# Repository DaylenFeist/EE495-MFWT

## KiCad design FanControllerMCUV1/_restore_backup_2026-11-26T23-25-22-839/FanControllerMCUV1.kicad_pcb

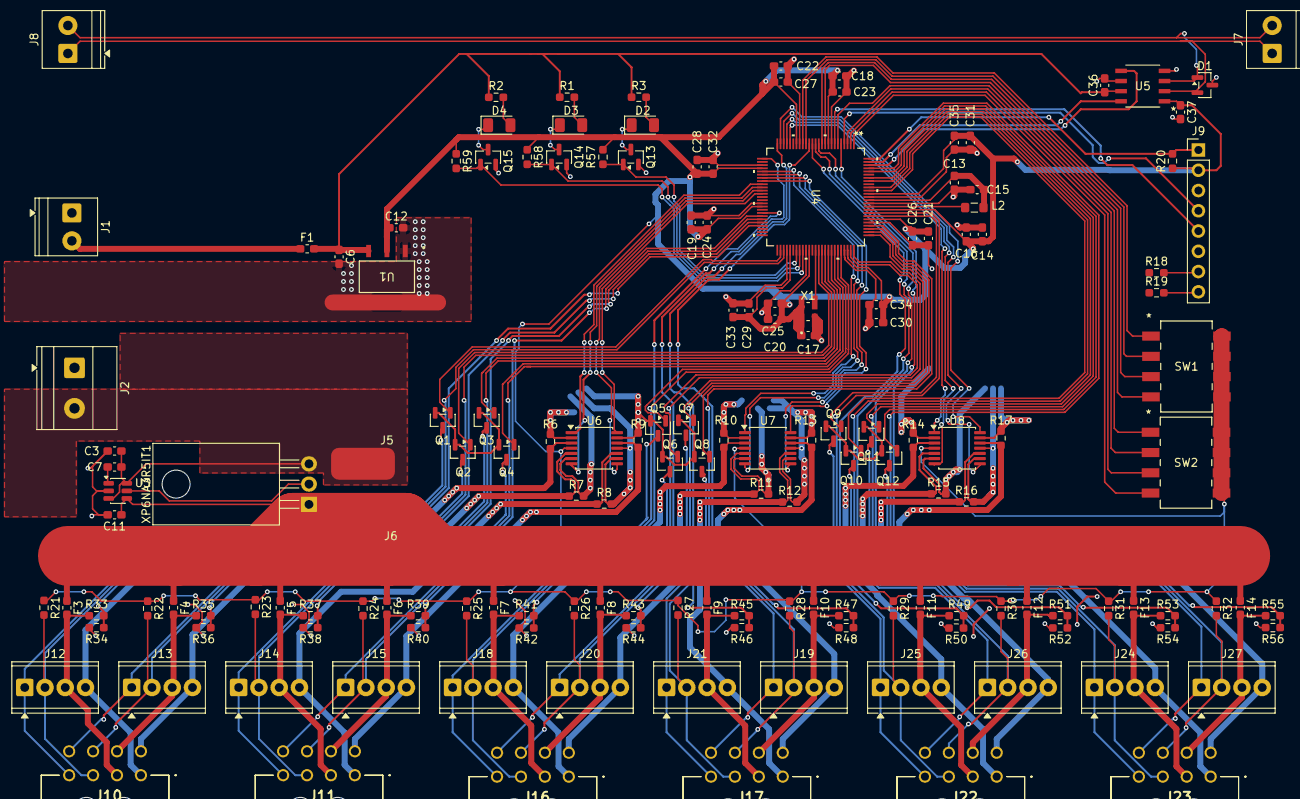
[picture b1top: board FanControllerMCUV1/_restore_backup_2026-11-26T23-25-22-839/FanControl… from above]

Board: 2 copper layers, 156 parts (0 on the bottom side), 121 nets.

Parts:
C3, C7, C11, C15, C16, C17, C18, C19, C20, C21, C23, C24, C25, C26, C27, C28, C29, C30, C31, C32, C33, C34, C35: 0.1u; C_0603_1608Metric_Pad1.08x0.95mm_HandSolder
C6, C12, C13, C14: 10u; C_0603_1608Metric_Pad1.08x0.95mm_HandSolder
C22: 1u; C_0603_1608Metric_Pad1.08x0.95mm_HandSolder
C36, C37: .1u; C_0603_1608Metric_Pad1.08x0.95mm_HandSolder
D1: NUP2105L; SOT-23
D2: GLED; LED_1206_3216Metric
D3: YLED; LED_1206_3216Metric
D4: RLED; LED_1206_3216Metric
F1, F3, F4, F5, F6, F7, F8, F9, F10, F11, F12, F13, F14: Fuse; Fuse_0603_1608Metric_Pad1.05x0.95mm_HandSolder
J1: Screw_Terminal_01x02; TerminalBlock_Phoenix_PT-1,5-2-3.5-H_1x02_P3.50mm_Horizontal
J2: Screw_Terminal_01x02; TerminalBlock_Phoenix_MKDS-1,5-2-5.08_1x02_P5.08mm_Horizont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
J5, J6: Conn_01x01_Pin; SolderWirePad_1x01_SMD_4x8mm
J7: CAN-IN; TerminalBlock_Phoenix_PT-1,5-2-3.5-H_1x02_P3.50mm_Horizontal
J8: CAN-OUT; TerminalBlock_Phoenix_PT-1,5-2-3.5-H_1x02_P3.50mm_Horizontal
J9: Conn_01x08_Pin; PinHeader_1x08_P2.54mm_Vertical
J10, J11, J16, J17, J22, J23: 3-794618-8; 37946188
J12, J13, J14, J15, J18, J19, J20, J21, J24, J25, J26, J27: Screw_Terminal_01x04; TerminalBlock_Phoenix_MPT-0,5-4-2.54_1x04_P2.54mm_Horizontal
L2: SRN2012T-100K; L_0805_2012Metric_Pad1.05x1.20mm_HandSolder
Q1, Q2, Q3, Q4, Q5, Q6, Q7, Q8, Q9, Q10, Q11, Q12, Q13, Q14, Q15: 2N7002; SOT-23
R1, R2: 300; R_0603_1608Metric_Pad0.98x0.95mm_HandSolder
R3: 180; R_0603_1608Metric_Pad0.98x0.95mm_HandSolder
R6, R7, R8, R9, R10, R11, R12, R13, R14, R15, R16, R17: 20m; R_0603_1608Metric_Pad0.98x0.95mm_HandSolder
R18, R19: DNP; R_0603_1608Metric_Pad0.98x0.95mm_HandSolder
R20, R21, R22, R23, R24, R25, R26, R27, R28, R29, R30, R31, R32, R34, R36, R38, R40, R42, R44, R46, R48, R50, R52, R54, R56: 10k; R_0603_1608Metric_Pad0.98x0.95mm_HandSolder
R33, R35, R37, R39, R41, R43, R45, R47, R49, R51, R53, R55: 240k; R_0603_1608Metric_Pad0.98x0.95mm_HandSolder
R57, R58, R59: 100k; R_0603_1608Metric_Pad0.98x0.95mm_HandSolder
SW1, SW2: SW_DIP_x04; DS04-254-2-04BK-SMT_CUD
U1: NCP1117ST33T3G; SOT223-3_ONS
U3: LM74700; SOT-23-6
U4: dsPIC33AK512MC510-I/PT; TQFP100_PT_MCH
U5: TCAN1462VDRQ1; SOIC8_D_TEX
U6, U7, U8: INA4180A2; TSSOP-14_4.4x5mm_P0.65mm
X1: DSC6011JI2B-008.0000; VLGA4_AUA_MCH
XP6NA3R5IT1: NMOS; TO-220-3_Horizontal_TabDown

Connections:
*MCLR: J9.1, R20.2, U4.100 (*MCLR)
+5V: C6.1, C36.1, F1.2, R1.1, R2.1, R3.1, U1.3 (INPUT), U5.3 (VCC)
+48V: C3.1, C7.1, J2.2, J5.1 (Pin_1_1), U3.3 (EN), U3.6 (ANODE), XP6NA3R5IT1.3 (S)
/MCU/CAN+: D1.1 (K), J7.2, J8.2, U5.7 (CANH)
/MCU/CAN-: D1.2 (K), J7.1, J8.1, U5.6 (CANL)
AVDD: C12.1, C14.2, C16.2, C17.1, C18.1, C19.1, C20.1, C21.1, C22.1, C23.1, C24.1, C25.1, C26.1, C27.1, C28.1, C29.1, C30.1, C31.1, C32.1, C33.1, C34.1, C35.1, C37.1, J9.2, R20.1, R21.1, R22.1, R23.1, R24.1, R25.1, R26.1, R27.1, R28.1, R29.1, R30.1, R31.1, R32.1, R57.1, R58.1, R59.1, SW1.5, SW1.6, SW1.7, SW1.8, SW2.5, SW2.6, SW2.7, SW2.8, U1.2 (OUTPUT), U4.9 (VDD), U4.19 (AVDD), U4.29 (VDD), U4.41 (VDD), U4.55 (VDD), U4.61 (VDD), U4.73 (VDD), U4.81 (VDD), U4.84 (SWVDD), U4.89 (VDD), U5.5 (NC,_VIO), U6.4 (VS), U7.4 (VS), U8.4 (VS), X1.1 (*STDBY), X1.4 (VDD)
AVSS: C3.2, C6.2, C11.2, C12.2, C13.2, C14.1, C15.2, C16.1, C17.2, C18.2, C19.2, C20.2, C21.2, C22.2, C23.2, C24.2, C25.2, C26.2, C27.2, C28.2, C29.2, C30.2, C31.2, C32.2, C33.2, C34.2, C35.2, C36.2, C37.2, D1.3 (A), J1.1, J2.1, J9.3, Q1.2 (S), Q2.2 (S), Q3.2 (S), Q4.2 (S), Q5.2 (S), Q6.2 (S), Q7.2 (S), Q8.2 (S), Q9.2 (S), Q10.2 (S), Q11.2 (S), Q12.2 (S), Q13.2 (S), Q14.2 (S), Q15.2 (S), R6.2, R7.2, R8.2, R9.2, R10.2, R11.2, R12.2, R13.2, R14.2, R15.2, R16.2, R17.2, R34.2, R36.2, R38.2, R40.2, R42.2, R44.2, R46.2, R48.2, R50.2, R52.2, R54.2, R56.2, U1.1 (ADJUST/GROUND), U3.2 (GND), U4.8 (VSS), U4.18 (AVSS), U4.28 (VSS), U4.40 (VSS), U4.54 (VSS), U4.60 (VSS), U4.72 (VSS), U4.80 (VSS), U4.86 (SWVSS), U4.88 (VSS), U5.2 (GND), U5.8 (STB), U6.2 (-), U6.6 (-), U6.9 (-), U6.11 (GND), U6.13 (-), U7.2 (-), U7.6 (-), U7.9 (-), U7.11 (GND), U7.13 (-), U8.2 (-), U8.6 (-), U8.9 (-), U8.11 (GND), U8.13 (-), X1.2 (GND)
CAN1_RX: U4.99 (CVDTX18/RP57/ASDA2/IOMAF3/RD8), U5.4 (RXD)
CAN1_TX: U4.98 (CVDTX17/RP56/ASCL2/IOMAF4/RD7), U5.1 (TXD)
CLKI: U4.63 (OSCI/CLKI/RP34/IOMAF6/RC1), X1.3 (OUT)
Current_Amp1: U4.34 (AD2AN4/CVDAN24/CVDTX8/CMP2D/RP25/RB8), U6.1
Current_Amp2: U4.35 (AD2ANN1/AD2AN3/CVDAN25/CVDTX9/RP26/RB9), U6.7
Current_Amp3: U4.36 (AD2AN5/CVDAN31/CVDTX15/RP32/RB15), U6.8
Current_Amp4: U4.37 (AD3AN4/CVDTX29/RP81/RF0), U6.14
Current_Amp5: U4.30 (AD3ANN1/AD3AN3/CVDAN29/CVDTX13/RP30/RB13), U7.1
Current_Amp6: U4.31 (OA2OUT/AD2AN0/CVDAN16/CVDTX0/CMP2A/RP17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), U7.7
Current_Amp7: U4.32 (TMS/OA2IN-/AD2ANN2/AD2AN2/CVDAN17/CVDTX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), U7.8
Current_Amp8: U4.33 (OA2IN+/AD2AN1/CVDAN18/CVDTX2/CMP2B/RP19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), U7.14
Current_Amp9: U4.21 (OA1OUT/AD1AN0/CVDAN2/CMP1A/RP3/RA2), U8.1
Current_Amp10: U4.22 (OA1IN-/AD1ANN2/AD1AN2/CVDAN3/CMPCN/CMP1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), U8.7
Current_Amp11: U4.23 (OA1IN+/AD1AN1/AD5AN4/CVDAN4/CMP1B/RP5/R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), U8.8
Current_Amp12: U4.24 (OA3OUT/AD3AN0/CVDAN5/CMP3A/RP6/INT0/RA5), U8.14
DIP1: SW2.4, U4.1 (CVDTX19/RP65/RE0)
DIP2: SW2.3, U4.2 (CVDTX20/RP66/RE1)
DIP3: SW2.2, U4.3 (CVDAN12/RP13/RA12)
DIP4: SW2.1, U4.6 (CVDTX22/RP68/RE3)
DIP5: SW1.4, U4.10 (CVDTX21/RP67/RE2)
DIP6: SW1.3, U4.11 (CVDAN13/RP14/RA13)
DIP7: SW1.2, U4.16 (CVDTX23/RP69/RE4)
DIP8: SW1.1, U4.17 (CVDAN15/RP16/RA15)
GLED: Q13.1 (G), R57.2, U4.57 (RP42/SDO2/IOMBF2/RC9)
unnamed: D2.2 (A), R3.2
unnamed: D2.1 (K), Q13.3 (D)
unnamed: D3.2 (A), R1.2
unnamed: D3.1 (K), Q14.3 (D)
unnamed: D4.2 (A), R2.2
unnamed: D4.1 (K), Q15.3 (D)
unnamed: F1.1, J1.2
unnamed: C11.1, F3.1, F4.1, F5.1, F6.1, F7.1, F8.1, F9.1, F10.1, F11.1, F12.1, F13.1, F14.1, J6.1 (Pin_1_1), U3.4 (CATHODE), XP6NA3R5IT1.1 (D)
unnamed: J9.7, R18.2
unnamed: J9.8, R19.2
unnamed: U3.5 (GATE), XP6NA3R5IT1.2 (G)
unnamed: C7.2, U3.1 (VCAP)
unnamed: L2.1, U4.85 (LX)
unnamed: C13.1, C15.1, L2.2, U4.87 (VDDCORE)
PGC: J9.5, U4.7 (PGC2/DACOUT1/AD5AN1/CVDAN1/CMP4D/RP2/RA1)
PGD: J9.4, U4.4 (PGD2/AD3AN5/CVDAN0/RP1/SCL2/IOMAF2/RA0)
RLED: Q15.1 (G), R59.2, U4.59 (RP40/SDA3/IOMAF7/RC7)
Volt_Sample1_Reduced: R33.2, R34.1, U4.47 (AD4AN4/CVDAN26/CVDTX10/RP27/SCK2/IOMAF1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)
Volt_Sample2_Reduced: R35.2, R36.1, U4.46 (AD4ANN1/AD4AN2/CVDAN23/CVDTX7/CMP4C/IBI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)
Volt_Sample3_Reduced: R37.2, R38.1, U4.45 (AD4ANN2/AD4AN1/CVDAN22/CVDTX6/CMP/IBIAS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)
Volt_Sample4_Reduced: R39.2, R40.1, U4.44 (PGC1/AD4AN0/CVDAN20/CVDTX4/CMP4B/RP21/S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)
Volt_Sample5_Reduced: R41.2, R42.1, U4.43 (PGD1/AD4AN3/CVDAN19/CVDTX3/CMP4A/RP20/S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)
Volt_Sample6_Reduced: R43.2, R44.1, U4.26 (OA3IN+/AD3AN1/AD4AN5/CVDAN21/CVDTX5/CMP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)
Volt_Sample7_Reduced: R45.2, R46.1, U4.25 (OA3IN-/AD3ANN2/AD3AN2/CVDAN6/CMPDN/CMP3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)
Volt_Sample8_Reduced: R47.2, R48.1, U4.15 (AD1ANN1/AD1AN4/CVDAN10/CMPEN/RP11/RA10)
Volt_Sample9_Reduced: R49.2, R50.1, U4.14 (UREF/AD1AN3/CVDAN9/IBIAS2/ISRC2/RP10/RA9)
Volt_Sample10_Reduced: R51.2, R52.1, U4.13 (DACOUT2/AD5AN3/CVDAN8/IBIAS3/ISRC3/RP9/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)
Volt_Sample11_Reduced: R53.2, R54.1, U4.12 (AD5ANN2/AD5AN2/CVDAN11/CMPFN/RP12/RA11)
Volt_Sample12_Reduced: R55.2, R56.1, U4.5 (AD5ANN1/AD5AN0/CVDAN7/RP8/SDA2/IOMAF1/R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)
YLED: Q14.1 (G), R58.2, U4.58 (RP39/SCL3/RC6)
fan1_48V: F3.2, J10.2, J12.3, R33.1
fan1_PWM: J10.4, J12.1, Q1.3 (D)
fan1_PWM_3V3: Q1.1 (G), U4.52 (RP98/APWM4H/IOMBD11/RG1)
fan1_RTN: J10.1, J12.4, R6.1, U6.3 (+)
fan1_TACH: J10.3, J12.2, R21.2, U4.53 (RP99/APWM4L/IOMBD10/RG2)
fan2_48V: F4.2, J10.6, J13.3, R35.1
fan2_PWM: J10.8, J13.1, Q2.3 (D)
fan2_PWM_3V3: Q2.1 (G), U4.64 (PGC3/RP35/PWM4H/IOMAD7/RC2)
fan2_RTN: J10.5, J13.4, R7.1, U6.5 (+)
fan2_TACH: J10.7, J13.2, R22.2, U4.65 (PGD3/RP38/PWM4L/IOMAD6/RC5)
fan3_48V: F5.2, J11.2, J14.3, R37.1
fan3_PWM: J11.4, J14.1, Q3.3 (D)
fan3_PWM_3V3: Q3.1 (G), U4.66 (RP36/PWM3H/IOMAD5/RC3)
fan3_RTN: J11.1, J14.4, R8.1, U6.10 (+)
fan3_TACH: J11.3, J14.2, R23.2, U4.67 (RP37/PWM3L/IOMAD4/RC4)
fan4_48V: F6.2, J11.6, J15.3, R39.1
fan4_PWM: J11.8, J15.1, Q4.3 (D)
fan4_PWM_3V3: Q4.1 (G), U4.68 (RP43/PWM7H/IOMBD5/IOMBF1/RC10)
fan4_RTN: J11.5, J15.4, R9.1, U6.12 (+)
fan4_TACH: J11.7, J15.2, R24.2, U4.69 (RP44/PWM7L/IOMBD4/IOMBF0/RC11)
fan5_48V: F7.2, J16.2, J18.3, R41.1
fan5_PWM: J16.4, J18.1, Q5.3 (D)
fan5_PWM_3V3: Q5.1 (G), U4.70 (RP45/PWM8H/IOMBD7/RC12)
fan5_RTN: J16.1, J18.4, R10.1, U7.3 (+)
fan5_TACH: J16.3, J18.2, R25.2, U4.71 (RP46/PWM8L/IOMBD6/RC13)
fan6_48V: F8.2, J16.6, J20.3, R43.1
fan6_PWM: J16.8, J20.1, Q6.3 (D)
fan6_PWM_3V3: Q6.1 (G), U4.74 (RP47/APWM3H/IOMBD9/RC14)
fan6_RTN: J16.5, J20.4, R11.1, U7.5 (+)
fan6_TACH: J16.7, J20.2, R26.2, U4.75 (RP48/APWM3L/IOMBD8/RC15)
fan7_48V: F9.2, J17.2, J21.3, R45.1
fan7_PWM: J17.4, J21.1, Q7.3 (D)
fan7_PWM_3V3: Q7.1 (G), U4.76 (RP58/PWM6H/IOMBD3/IOMBF7/RD9)
fan7_RTN: J17.1, J21.4, R12.1, U7.10 (+)
fan7_TACH: J17.3, J21.2, R27.2, U4.77 (RP59/PWM6L/IOMBD2/IOMAF9/IOMBF9/RD10)
fan8_48V: F10.2, J17.6, J19.3, R47.1
fan8_PWM: J17.8, J19.1, Q8.3 (D)
fan8_PWM_3V3: Q8.1 (G), U4.78 (RP49/PWM2H/IOMAD3/RD0)
fan8_RTN: J17.5, J19.4, R13.1, U7.12 (+)
fan8_TACH: J17.7, J19.2, R28.2, U4.79 (TCK/RP50/PWM2L/IOMAD2/RD1)
fan9_48V: F11.2, J22.2, J25.3, R49.1
fan9_PWM: J22.4, J25.1, Q9.3 (D)
fan9_PWM_3V3: Q9.1 (G), U4.82 (TDO/RP51/PWM1H/IOMAD1/RD2)
fan9_RTN: J22.1, J25.4, R14.1, U8.3 (+)
fan9_TACH: J22.3, J25.2, R29.2, U4.83 (TDI/RP52/PWM1L/IOMAD0/RD3)
fan10_48V: F12.2, J22.6, J26.3, R51.1
fan10_PWM: J22.8, J26.1, Q10.3 (D)
fan10_PWM_3V3: Q10.1 (G), U4.90 (RP54/PWM5H/ASCL1/IOMBD1/RD5)
fan10_RTN: J22.5, J26.4, R15.1, U8.5 (+)
fan10_TACH: J22.7, J26.2, R30.2, U4.91 (RP55/PWM5L/ASDA1/IOMBD0/RD6)
fan11_48V: F13.2, J23.2, J24.3, R53.1
fan11_PWM: J23.4, J24.1, Q11.3 (D)
fan11_PWM_3V3: Q11.1 (G), U4.93 (RP60/APWM1H/IOMAD9/IOMAF8/IOMBF8/RD11)
fan11_RTN: J23.1, J24.4, R16.1, U8.10 (+)
fan11_TACH: J23.3, J24.2, R31.2, U4.94 (RP61/ASDA3/RD12)
fan12_48V: F14.2, J23.6, J27.3, R55.1
fan12_PWM: J23.8, J27.1, Q12.3 (D)
fan12_PWM_3V3: Q12.1 (G), U4.96 (RP63/APWM2H/IOMAD11/RD14)
fan12_RTN: J23.5, J27.4, R17.1, U8.12 (+)
fan12_TACH: J23.7, J27.2, R32.2, U4.97 (RP64/APWM2L/IOMAD10/IOMBF5/RD15)

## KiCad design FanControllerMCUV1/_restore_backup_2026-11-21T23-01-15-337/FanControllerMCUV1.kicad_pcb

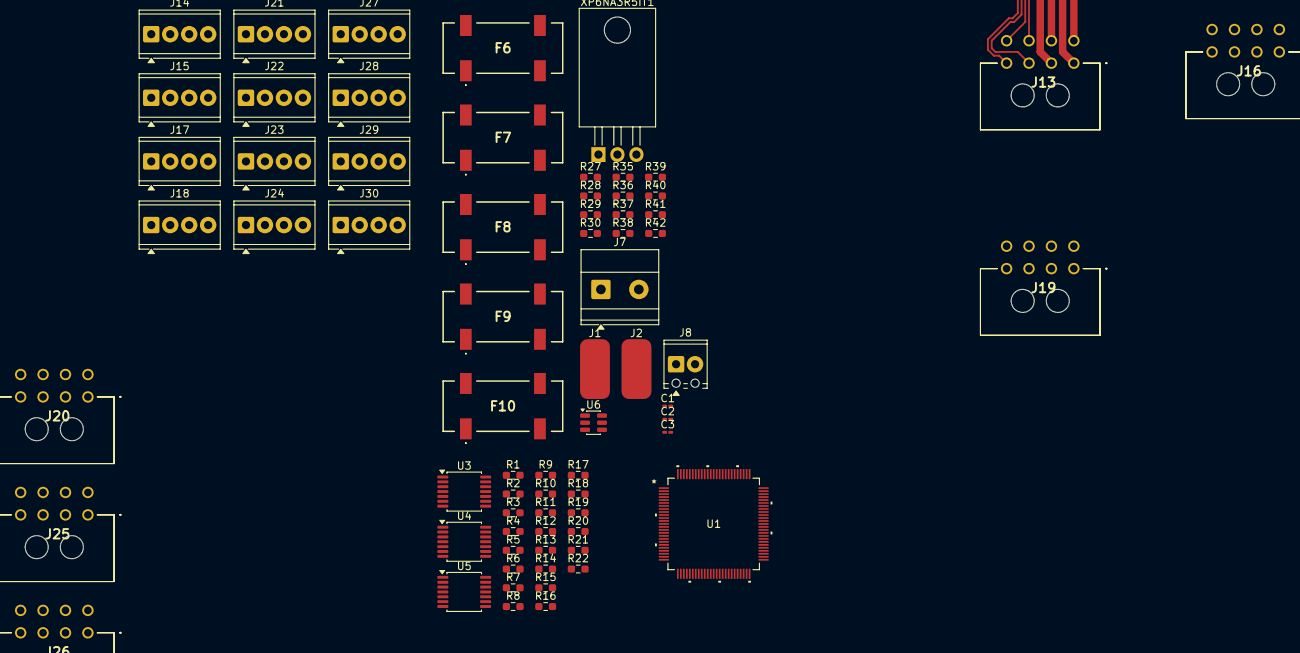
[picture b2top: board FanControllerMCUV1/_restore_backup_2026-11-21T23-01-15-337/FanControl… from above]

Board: 2 copper layers, 70 parts (0 on the bottom side), 62 nets.

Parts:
C1, C2, C3: 0.1u; C_0201_0603Metric_Pad0.64x0.40mm_HandSolder
F6: 20A; 3588
F7, F8, F9: 6A; 3588
F10: 2A; 3588
J1, J2: Conn_01x01_Pin; SolderWirePad_1x01_SMD_4x8mm
J7: Screw_Terminal_01x02; TerminalBlock_Phoenix_MKDS-1,5-2-5.08_1x02_P5.08mm_Horizont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
J8: Screw_Terminal_01x02; TerminalBlock_Phoenix_MPT-0,5-2-2.54_1x02_P2.54mm_Horizontal
J13, J16, J19, J20, J25, J26: 3-794618-8; 37946188
J14, J15, J17, J18, J21, J22, J23, J24, J27, J28, J29, J30: Screw_Terminal_01x04; TerminalBlock_Phoenix_MPT-0,5-4-2.54_1x04_P2.54mm_Horizontal
R1, R2, R3, R4, R5, R6, R7, R8, R9, R10, R11, R12, R13, R14, R15, R18, R20, R22: 10k; R_0603_1608Metric_Pad0.98x0.95mm_HandSolder
R16, R17, R19, R21: 240k; R_0603_1608Metric_Pad0.98x0.95mm_HandSolder
R27, R28, R29, R30, R35, R36, R37, R38, R39, R40, R41, R42: 10m; R_0603_1608Metric_Pad0.98x0.95mm_HandSolder
U1: dsPIC33AK512MC510-I/PT; TQFP100_PT_MCH
U3, U4, U5: INA4180A1; TSSOP-14_4.4x5mm_P0.65mm
U6: LM74700; SOT-23-6
XP6NA3R5IT1: NMOS; TO-220-3_Horizontal_TabDown

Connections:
+2V5: R13.2, R14.1
+3V3: R1.1, R2.1, R3.1, R4.1, R5.1, R6.1, R7.1, R8.1, R9.1, R10.1, R11.1, R12.1, U3.4 (VS), U4.4 (VS), U5.4 (VS)
+5V: F10.2, F10.3, R13.1
+48V: F6.1, F6.4, J7.2
GND: C2.2, C3.2, J7.1, J8.1, R14.2, R15.2, R18.2, R20.2, R22.2, R27.2, R28.2, R29.2, R30.2, R35.2, R36.2, R37.2, R38.2, R39.2, R40.2, R41.2, R42.2, U3.2 (-), U3.6 (-), U3.9 (-), U3.11 (GND), U3.13 (-), U4.2 (-), U4.6 (-), U4.9 (-), U4.11 (GND), U4.13 (-), U5.2 (-), U5.6 (-), U5.9 (-), U5.11 (GND), U5.13 (-), U6.2 (GND)
unnamed: C1.1, C3.1, F6.2, F6.3, J1.1 (Pin_1_1), U6.6 (ANODE), XP6NA3R5IT1.3 (S)
unnamed: C2.1, F7.1, F7.4, F8.1, F8.4, F9.1, F9.4, J2.1 (Pin_1_1), U6.4 (CATHODE), XP6NA3R5IT1.1 (D)
unnamed: F10.1, F10.4, J8.2
unnamed: U6.5 (GATE), XP6NA3R5IT1.2 (G)
unnamed: C1.2, U6.1 (VCAP)
Volt_Sample1_Reduced: R15.1, R16.2
Volt_Sample2_Reduced: R17.2, R18.1
Volt_Sample3_Reduced: R19.2, R20.1
Volt_Sample4_Reduced: R21.2, R22.1
fan1_48V: F7.2, F7.3, J13.2, J14.1, R16.1
fan1_PWM: J13.4, J14.3
fan1_RTN: J13.1, J14.2, R27.1, U3.3 (+)
fan1_TACH: J13.3, J14.4, R1.2
fan2_48V: J13.6, J15.1, R17.1
fan2_PWM: J13.8, J15.3
fan2_RTN: J13.5, J15.2, R28.1, U3.5 (+)
fan2_TACH: J13.7, J15.4, R2.2
fan3_48V: J16.2, J17.1, R19.1
fan3_PWM: J16.4, J17.3
fan3_RTN: J16.1, J17.2, R29.1, U3.10 (+)
fan3_TACH: J16.3, J17.4, R3.2
fan4_48V: J16.6, J18.1, R21.1
fan4_PWM: J16.8, J18.3
fan4_RTN: J16.5, J18.2, R30.1, U3.12 (+)
fan4_TACH: J16.7, J18.4, R4.2
fan5_48V: F8.2, F8.3, J19.4, J21.1
fan5_PWM: J19.2, J21.3
fan5_RTN: J19.3, J21.2, R35.1, U4.3 (+)
fan5_TACH: J19.1, J21.4, R5.2
fan6_48V: J19.8, J22.1
fan6_PWM: J19.6, J22.3
fan6_RTN: J19.7, J22.2, R36.1, U4.5 (+)
fan6_TACH: J19.5, J22.4, R6.2
fan7_48V: J20.4, J23.1
fan7_PWM: J20.2, J23.3
fan7_RTN: J20.3, J23.2, R37.1, U4.10 (+)
fan7_TACH: J20.1, J23.4, R7.2
fan8_48V: J20.8, J24.1
fan8_PWM: J20.6, J24.3
fan8_RTN: J20.7, J24.2, R38.1, U4.12 (+)
fan8_TACH: J20.5, J24.4, R8.2
fan9_48V: J25.4, J27.1
fan9_PWM: J25.2, J27.3
fan9_RTN: J25.3, J27.2, R39.1, U5.3 (+)
fan9_TACH: J25.1, J27.4, R9.2
fan10_48V: F9.2, F9.3, J25.8, J28.1
fan10_PWM: J25.6, J28.3
fan10_RTN: J25.7, J28.2, R40.1, U5.5 (+)
fan10_TACH: J25.5, J28.4, R10.2
fan11_48V: J26.4, J29.1
fan11_PWM: J26.2, J29.3
fan11_RTN: J26.3, J29.2, R41.1, U5.10 (+)
fan11_TACH: J26.1, J29.4, R11.2
fan12_48V: J26.8, J30.1
fan12_PWM: J26.6, J30.3
fan12_RTN: J26.7, J30.2, R42.1, U5.12 (+)
fan12_TACH: J26.5, J30.4, R12.2

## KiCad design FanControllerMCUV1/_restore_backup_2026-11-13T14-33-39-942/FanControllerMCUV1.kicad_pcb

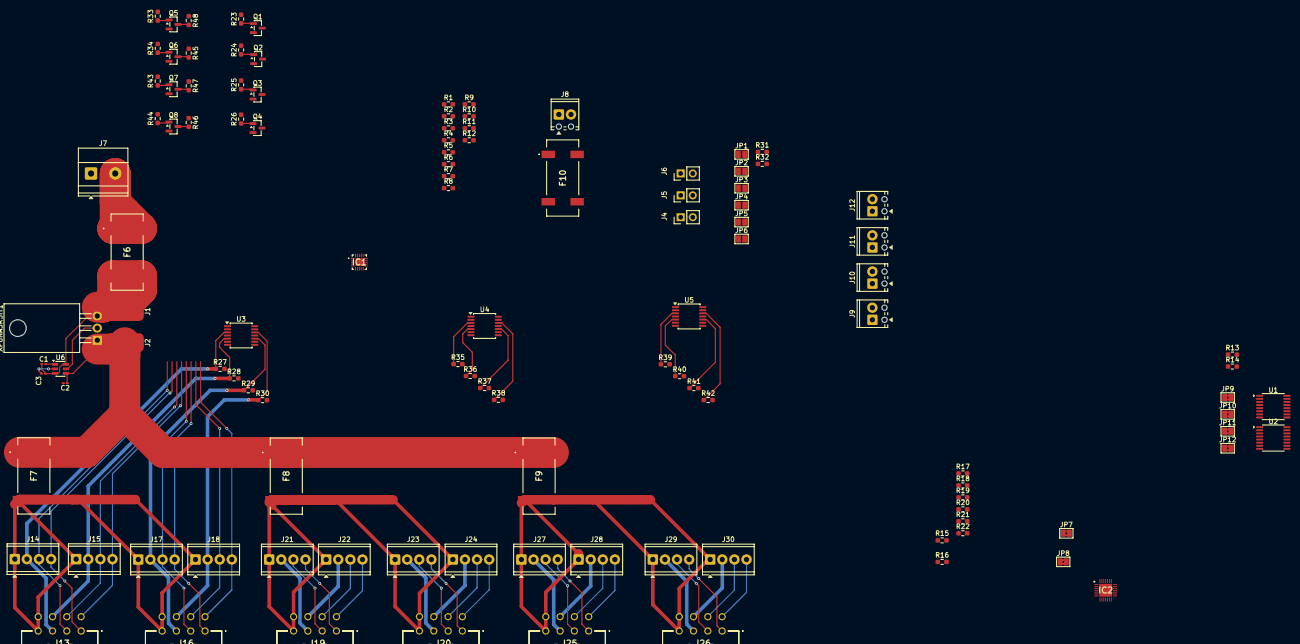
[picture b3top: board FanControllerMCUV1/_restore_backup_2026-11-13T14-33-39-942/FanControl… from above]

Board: 2 copper layers, 114 parts (0 on the bottom side), 85 nets.

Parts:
C1, C2, C3: 0.1u; C_0201_0603Metric_Pad0.64x0.40mm_HandSolder
F6: 20A; 3588
F7, F8, F9: 6A; 3588
F10: 2A; 3588
IC1: IS31FL3292-QFLS4-TR; IS31FL3292QFLS4TR
IC2: MAX31790ATI+T; QFN40P400X400X80-29N
J1, J2: Conn_01x01_Pin; SolderWirePad_1x01_SMD_4x8mm
J4, J5, J6: Conn_01x02_Pin; PinHeader_1x02_P2.54mm_Vertical
J7: Screw_Terminal_01x02; TerminalBlock_Phoenix_MKDS-1,5-2-5.08_1x02_P5.08mm_Horizont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
J8, J9, J10, J11, J12: Screw_Terminal_01x02; TerminalBlock_Phoenix_MPT-0,5-2-2.54_1x02_P2.54mm_Horizontal
J13, J16, J19, J20, J25, J26: 3-794618-8; 37946188
J14, J15, J17, J18, J21, J22, J23, J24, J27, J28, J29, J30: Screw_Terminal_01x04; TerminalBlock_Phoenix_MPT-0,5-4-2.54_1x04_P2.54mm_Horizontal
JP1, JP2, JP3, JP4, JP5, JP6: SolderJumper_2_Open; SolderJumper-2_P1.3mm_Open_Pad1.0x1.5mm
JP7, JP8, JP9, JP10, JP11, JP12: SolderJumper_2_Bridged; SolderJumper-2_P1.3mm_Bridged2Bar_Pad1.0x1.5mm
Q1, Q2, Q3, Q4, Q5, Q6, Q7, Q8: 2N7002; SOT-23
R1, R2, R3, R4, R5, R6, R7, R8, R9, R10, R11, R12, R13, R14, R15, R18, R20, R22, R23, R24, R25, R26, R33, R34, R43, R44, R45, R46, R47, R48: 10k; R_0603_1608Metric_Pad0.98x0.95mm_HandSolder
R16, R17, R19, R21: 240k; R_0603_1608Metric_Pad0.98x0.95mm_HandSolder
R27, R28, R29, R30, R35, R36, R37, R38, R39, R40, R41, R42: 10m; R_0603_1608Metric_Pad0.98x0.95mm_HandSolder
R31, R32: 4.7k; R_0603_1608Metric_Pad0.98x0.95mm_HandSolder
U1, U2: ADS7828; TSSOP-16_4.4x5mm_P0.65mm
U3, U4, U5: INA4180A1; TSSOP-14_4.4x5mm_P0.65mm
U6: LM74700; SOT-23-6
XP6NA3R5IT1: NMOS; TO-220-3_Horizontal_TabDown

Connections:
+2V5: R13.2, R14.1, U1.10 (REF), U2.10 (REF)
+5V: F10.2, F10.3, IC1.1 (VCC), IC1.13 (SDB), IC2.21 (VCC), IC2.27 (~FULL_SPEED), JP12.2 (B), R1.1, R2.1, R3.1, R4.1, R5.1, R6.1, R7.1, R8.1, R9.1, R10.1, R11.1, R12.1, R13.1, R23.1, R24.1, R25.1, R26.1, R31.1, R32.1, R33.1, R34.1, R43.1, R44.1, R45.1, R46.1, R47.1, R48.1, U1.16 (VDD), U2.16 (VDD), U3.4 (VS), U4.4 (VS), U5.4 (VS)
+48V: F6.1, F6.4, J7.2
ADS7828_1_SCL: J10.1, JP4.1 (A), JP5.2 (B), U2.14 (SCL)
ADS7828_1_SDA: J10.2, JP1.1 (A), JP2.2 (B), U2.15 (SDA)
ADS7828_2_SCL: J11.1, JP5.1 (A), JP6.2 (B), U1.14 (SCL)
ADS7828_2_SDA: J11.2, JP2.1 (A), JP3.2 (B), U1.15 (SDA)
CURR_SINK_5: IC1.8 (OUT5), Q1.1 (G), R23.2
CURR_SINK_6: IC1.9 (OUT6), Q3.1 (G), R25.2
CURR_SINK_7: IC1.10 (OUT7), Q2.1 (G), R24.2
CURR_SINK_8: IC1.11 (OUT8), Q4.1 (G), R26.2
CURR_SINK_9: IC1.12 (OUT9), Q5.1 (G), R33.2
CURR_SINK_10: IC1.14 (OUT10), Q7.1 (G), R43.2
CURR_SINK_11: IC1.15 (OUT11), Q6.1 (G), R34.2
CURR_SINK_12: IC1.2 (OUT12), Q8.1 (G), R44.2
Current_Amp2: U2.2 (CH1), U3.7
Current_Amp3: U2.3 (CH2), U3.8
Current_Amp4: U2.4 (CH3), U3.14
Current_Amp5: U2.5 (CH4), U3.1, U4.1
Current_Amp6: U2.6 (CH5), U4.7
Current_Amp7: U2.7 (CH6), U4.8
Current_Amp8: U2.8 (CH7), U4.14
Current_Amp9: U1.1 (CH0), U5.1
Current_Amp10: U1.2 (CH1), U5.7
Current_Amp11: U1.3 (CH2), U5.8
Current_Amp12: U1.4 (CH3), U5.14
GND: C2.2, C3.2, IC1.7 (GND_1), IC1.16 (AD), IC1.21 (GND_2), IC2.2 (SPIN_START), IC2.5 (WD_START), IC2.7 (XTAL1), IC2.8 (GND), IC2.25 (PWM_START0), IC2.26 (PWM_START1), IC2.29 (EP), J7.1, J8.1, JP7.1 (A), JP8.1 (A), JP9.1 (A), JP10.1 (A), JP11.1 (A), Q1.2 (S), Q2.2 (S), Q3.2 (S), Q4.2 (S), Q5.2 (S), Q6.2 (S), Q7.2 (S), Q8.2 (S), R14.2, R15.2, R18.2, R20.2, R22.2, R27.2, R28.2, R29.2, R30.2, R35.2, R36.2, R37.2, R38.2, R39.2, R40.2, R41.2, R42.2, U1.9 (GND), U1.11 (COM), U2.9 (GND), U2.11 (COM), U3.2 (-), U3.6 (-), U3.9 (-), U3.11 (GND), U3.13 (-), U4.2 (-), U4.6 (-), U4.9 (-), U4.11 (GND), U4.13 (-), U5.2 (-), U5.6 (-), U5.9 (-), U5.11 (GND), U5.13 (-), U6.2 (GND)
IS31FL_SCL: IC1.18 (SCL), J12.1, JP6.1 (A)
IS31FL_SDA: IC1.19 (SDA), J12.2, JP3.1 (A)
MAX31790_SCL: IC2.23 (SCL), J9.2, JP1.2 (B), R31.2
MAX31790_SDA: IC2.22 (SDA), J9.1, JP4.2 (B), R32.2
unnamed: IC2.4 (ADD0), J4.2, JP7.2 (B)
unnamed: IC2.3 (ADD1), J4.1, JP8.2 (B)
unnamed: C1.1, C3.1, F6.2, F6.3, J1.1 (Pin_1_1), U6.3 (EN), U6.6 (ANODE), XP6NA3R5IT1.3 (S)
unnamed: J5.1, JP10.2 (B), U2.12 (A0)
unnamed: J5.2, JP9.2 (B), U2.13 (A1)
unnamed: J6.1, JP12.1 (A), U1.12 (A0)
unnamed: J6.2, JP11.2 (B), U1.13 (A1)
unnamed: F10.1, F10.4, J8.2
unnamed: U6.5 (GATE), XP6NA3R5IT1.2 (G)
unnamed: C1.2, U6.1 (VCAP)
Volt_Sample1: C2.1, F7.1, F7.4, F8.1, F8.4, F9.1, F9.4, J2.1 (Pin_1_1), R16.1, U6.4 (CATHODE), XP6NA3R5IT1.1 (D)
Volt_Sample1_Reduced: R15.1, R16.2, U1.5 (CH4)
Volt_Sample2: F7.2, F7.3, J13.4, J13.8, J14.1, J15.1, J16.4, J16.8, J17.1, J18.1, R17.1
Volt_Sample2_Reduced: R17.2, R18.1, U1.6 (CH5)
Volt_Sample3: F8.2, F8.3, J19.4, J19.8, J20.4, J20.8, J21.1, J22.1, J23.1, J24.1, R19.1
Volt_Sample3_Reduced: R19.2, R20.1, U1.7 (CH6)
Volt_Sample4: F9.2, F9.3, J25.4, J25.8, J26.4, J26.8, J27.1, J28.1, J29.1, J30.1, R21.1
Volt_Sample4_Reduced: R21.2, R22.1, U1.8 (CH7)
fan1_PWM: IC1.3 (OUT1), J13.2, J14.3
fan1_RTN: J13.3, J14.2, R27.1, U3.3 (+)
fan1_TACH: IC2.19 (TACH1), J13.1, J14.4, R1.2
fan2_PWM: IC1.4 (OUT2), J13.6, J15.3
fan2_RTN: J13.7, J15.2, R28.1, U3.5 (+)
fan2_TACH: IC2.20 (PWMOUT1), J13.5, J15.4, R2.2
fan3_PWM: IC1.5 (OUT3), J16.2, J17.3
fan3_RTN: J16.3, J17.2, R29.1, U3.10 (+)
fan3_TACH: IC2.17 (TACH2), J16.1, J17.4, R3.2
fan4_PWM: IC1.6 (OUT4), J16.6, J18.3
fan4_RTN: J16.7, J18.2, R30.1, U3.12 (+)
fan4_TACH: IC2.18 (PWMOUT2), J16.5, J18.4, R4.2
fan5_PWM: J20.2, J23.3, Q1.3 (D)
fan5_RTN: J20.3, J23.2, R35.1, U4.3 (+)
fan5_TACH: IC2.15 (TACH3), J20.1, J23.4, R5.2
fan6_PWM: J20.6, J24.3, Q3.3 (D)
fan6_RTN: J20.7, J24.2, R36.1, U4.5 (+)
fan6_TACH: IC2.16 (PWMOUT3), J20.5, J24.4, R6.2
fan7_PWM: J19.2, J21.3, Q2.3 (D)
fan7_RTN: J19.3, J21.2, R37.1, U4.10 (+)
fan7_TACH: IC2.13 (TACH4), J19.1, J21.4, R7.2
fan8_PWM: J19.6, J22.3, Q4.3 (D)
fan8_RTN: J19.7, J22.2, R38.1, U4.12 (+)
fan8_TACH: IC2.14 (PWMOUT4), J19.5, J22.4, R8.2
fan9_PWM: J26.2, J29.3, Q5.3 (D), R48.2
fan9_RTN: J26.3, J29.2, R39.1, U5.3 (+)
fan9_TACH: IC2.11 (TACH5), J26.1, J29.4, R9.2
fan10_PWM: J26.6, J30.3, Q7.3 (D), R47.2
fan10_RTN: J26.7, J30.2, R40.1, U5.5 (+)
fan10_TACH: IC2.12 (PWMOUT5), J26.5, J30.4, R10.2
fan11_PWM: J25.2, J27.3, Q6.3 (D), R45.2
fan11_RTN: J25.3, J27.2, R41.1, U5.10 (+)
fan11_TACH: IC2.9 (TACH6), J25.1, J27.4, R11.2
fan12_PWM: J25.6, J28.3, Q8.3 (D), R46.2
fan12_RTN: J25.7, J28.2, R42.1, U5.12 (+)
fan12_TACH: IC2.10 (PWMOUT6), J25.5, J28.4, R12.2

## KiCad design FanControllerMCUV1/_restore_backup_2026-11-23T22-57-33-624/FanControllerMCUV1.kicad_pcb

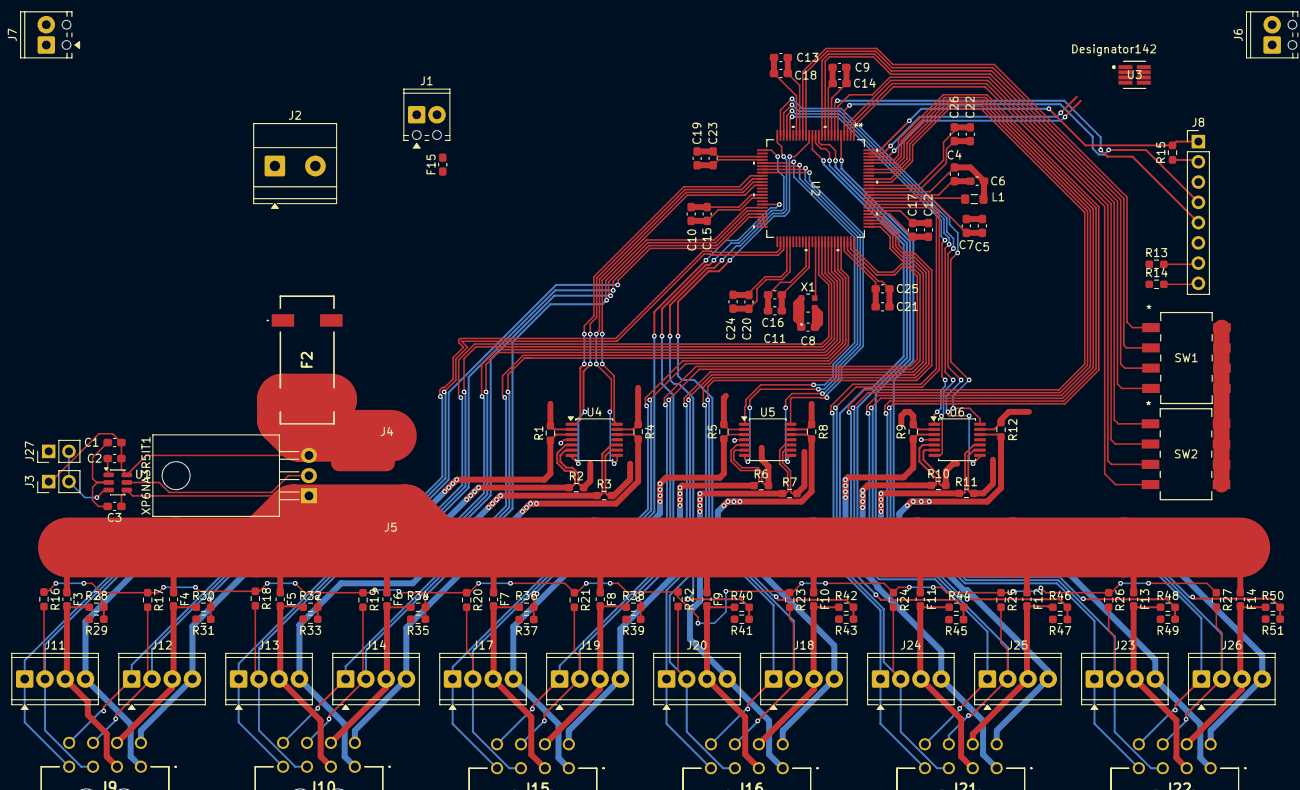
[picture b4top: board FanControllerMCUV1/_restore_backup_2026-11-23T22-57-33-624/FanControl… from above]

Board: 2 copper layers, 129 parts (0 on the bottom side), 99 nets.

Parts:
C1, C2, C3, C6, C7, C8, C9, C10, C11, C12, C14, C15, C16, C17, C18, C19, C20, C21, C22, C23, C24, C25, C26: 0.1u; C_0603_1608Metric_Pad1.08x0.95mm_HandSolder
C4, C5: 10u; C_0603_1608Metric_Pad1.08x0.95mm_HandSolder
C13: 1u; C_0603_1608Metric_Pad1.08x0.95mm_HandSolder
F2: 20A; 3588
F3, F4, F5, F6, F7, F8, F9, F10, F11, F12, F13, F14, F15: Fuse; Fuse_0603_1608Metric_Pad1.05x0.95mm_HandSolder
J1: Screw_Terminal_01x02; TerminalBlock_Phoenix_MPT-0,5-2-2.54_1x02_P2.54mm_Horizontal
J2: Screw_Terminal_01x02; TerminalBlock_Phoenix_MKDS-1,5-2-5.08_1x02_P5.08mm_Horizont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
J3, J27: Conn_01x02_Pin; PinHeader_1x02_P2.54mm_Vertical
J4, J5: Conn_01x01_Pin; SolderWirePad_1x01_SMD_4x8mm
J6: CAN-IN; TerminalBlock_Phoenix_MPT-0,5-2-2.54_1x02_P2.54mm_Horizontal
J7: CAN-OUT; TerminalBlock_Phoenix_MPT-0,5-2-2.54_1x02_P2.54mm_Horizontal
J8: Conn_01x08_Pin; PinHeader_1x08_P2.54mm_Vertical
J9, J10, J15, J16, J21, J22: 3-794618-8; 37946188
J11, J12, J13, J14, J17, J18, J19, J20, J23, J24, J25, J26: Screw_Terminal_01x04; TerminalBlock_Phoenix_MPT-0,5-4-2.54_1x04_P2.54mm_Horizontal
L1: SRN2012T-100K; L_0805_2012Metric_Pad1.05x1.20mm_HandSolder
R1, R2, R3, R4, R5, R6, R7, R8, R9, R10, R11, R12: 20m; R_0603_1608Metric_Pad0.98x0.95mm_HandSolder
R13, R14: DNP; R_0603_1608Metric_Pad0.98x0.95mm_HandSolder
R15, R16, R17, R18, R19, R20, R21, R22, R23, R24, R25, R26, R27, R29, R31, R33, R35, R37, R39, R41, R43, R45, R47, R49, R51: 10k; R_0603_1608Metric_Pad0.98x0.95mm_HandSolder
R28, R30, R32, R34, R36, R38, R40, R42, R44, R46, R48, R50: 240k; R_0603_1608Metric_Pad0.98x0.95mm_HandSolder
SW1, SW2: SW_DIP_x04; DS04-254-2-04BK-SMT_CUD
U1: LM74700; SOT-23-6
U2: dsPIC33AK512MC510-I/PT; TQFP100_PT_MCH
U3: TCAN1044AVDDFRQ1; DDF0008A-IPC_A
U4, U5, U6: INA4180A2; TSSOP-14_4.4x5mm_P0.65mm
X1: DSC6011JI2B-008.0000; VLGA4_AUA_MCH
XP6NA3R5IT1: NMOS; TO-220-3_Horizontal_TabDown

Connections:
3.3VSW: F15.1, J1.2
*MCLR: J8.1, R15.2, U2.100 (*MCLR)
+48V: F2.1, F2.4, J2.2
AVDD: C5.2, C7.2, C8.1, C9.1, C10.1, C11.1, C12.1, C13.1, C14.1, C15.1, C16.1, C17.1, C18.1, C19.1, C20.1, C21.1, C22.1, C23.1, C24.1, C25.1, C26.1, F15.2, J8.2, R15.1, R16.1, R17.1, R18.1, R19.1, R20.1, R21.1, R22.1, R23.1, R24.1, R25.1, R26.1, R27.1, SW1.5, SW1.6, SW1.7, SW1.8, SW2.5, SW2.6, SW2.7, SW2.8, U2.9 (VDD), U2.19 (AVDD), U2.29 (VDD), U2.41 (VDD), U2.55 (VDD), U2.61 (VDD), U2.73 (VDD), U2.81 (VDD), U2.84 (SWVDD), U2.89 (VDD), U4.4 (VS), U5.4 (VS), U6.4 (VS), X1.1 (*STDBY), X1.4 (VDD)
AVSS: C1.2, C3.2, C4.2, C5.1, C6.2, C7.1, C8.2, C9.2, C10.2, C11.2, C12.2, C13.2, C14.2, C15.2, C16.2, C17.2, C18.2, C19.2, C20.2, C21.2, C22.2, C23.2, C24.2, C25.2, C26.2, J1.1, J2.1, J8.3, R1.2, R2.2, R3.2, R4.2, R5.2, R6.2, R7.2, R8.2, R9.2, R10.2, R11.2, R12.2, R29.2, R31.2, R33.2, R35.2, R37.2, R39.2, R41.2, R43.2, R45.2, R47.2, R49.2, R51.2, U1.2 (GND), U2.8 (VSS), U2.18 (AVSS), U2.28 (VSS), U2.40 (VSS), U2.54 (VSS), U2.60 (VSS), U2.72 (VSS), U2.80 (VSS), U2.86 (SWVSS), U2.88 (VSS), U4.2 (-), U4.6 (-), U4.9 (-), U4.11 (GND), U4.13 (-), U5.2 (-), U5.6 (-), U5.9 (-), U5.11 (GND), U5.13 (-), U6.2 (-), U6.6 (-), U6.9 (-), U6.11 (GND), U6.13 (-), X1.2 (GND)
CLKI: U2.63 (OSCI/CLKI/RP34/IOMAF6/RC1), X1.3 (OUT)
Current_Amp1: U2.34 (AD2AN4/CVDAN24/CVDTX8/CMP2D/RP25/RB8), U4.1
Current_Amp2: U2.35 (AD2ANN1/AD2AN3/CVDAN25/CVDTX9/RP26/RB9), U4.7
Current_Amp3: U2.36 (AD2AN5/CVDAN31/CVDTX15/RP32/RB15), U4.8
Current_Amp4: U2.37 (AD3AN4/CVDTX29/RP81/RF0), U4.14
Current_Amp5: U2.30 (AD3ANN1/AD3AN3/CVDAN29/CVDTX13/RP30/RB13), U5.1
Current_Amp6: U2.31 (OA2OUT/AD2AN0/CVDAN16/CVDTX0/CMP2A/RP17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), U5.7
Current_Amp7: U2.32 (TMS/OA2IN-/AD2ANN2/AD2AN2/CVDAN17/CVDTX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), U5.8
Current_Amp8: U2.33 (OA2IN+/AD2AN1/CVDAN18/CVDTX2/CMP2B/RP19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), U5.14
Current_Amp9: U2.21 (OA1OUT/AD1AN0/CVDAN2/CMP1A/RP3/RA2), U6.1
Current_Amp10: U2.22 (OA1IN-/AD1ANN2/AD1AN2/CVDAN3/CMPCN/CMP1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), U6.7
Current_Amp11: U2.23 (OA1IN+/AD1AN1/AD5AN4/CVDAN4/CMP1B/RP5/R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), U6.8
Current_Amp12: U2.24 (OA3OUT/AD3AN0/CVDAN5/CMP3A/RP6/INT0/RA5), U6.14
DIP1: SW2.4, U2.1 (CVDTX19/RP65/RE0)
DIP2: SW2.3, U2.2 (CVDTX20/RP66/RE1)
DIP3: SW2.2, U2.3 (CVDAN12/RP13/RA12)
DIP4: SW2.1, U2.6 (CVDTX22/RP68/RE3)
DIP5: SW1.4, U2.10 (CVDTX21/RP67/RE2)
DIP6: SW1.3, U2.11 (CVDAN13/RP14/RA13)
DIP7: SW1.2, U2.16 (CVDTX23/RP69/RE4)
DIP8: SW1.1, U2.17 (CVDAN15/RP16/RA15)
unnamed: C1.1, C2.1, F2.2, F2.3, J3.1, J4.1 (Pin_1_1), U1.6 (ANODE), XP6NA3R5IT1.3 (S)
unnamed: C3.1, F3.1, F4.1, F5.1, F6.1, F7.1, F8.1, F9.1, F10.1, F11.1, F12.1, F13.1, F14.1, J5.1 (Pin_1_1), U1.4 (CATHODE), XP6NA3R5IT1.1 (D)
unnamed: J6.1, J7.1
unnamed: J6.2, J7.2
unnamed: J8.7, R13.2
unnamed: J8.8, R14.2
unnamed: J3.2, J27.2, U1.3 (EN)
unnamed: U1.5 (GATE), XP6NA3R5IT1.2 (G)
unnamed: C2.2, U1.1 (VCAP)
unnamed: L1.1, U2.85 (LX)
unnamed: C4.1, C6.1, L1.2, U2.87 (VDDCORE)
PGC: J8.5, U2.7 (PGC2/DACOUT1/AD5AN1/CVDAN1/CMP4D/RP2/RA1)
PGD: J8.4, U2.4 (PGD2/AD3AN5/CVDAN0/RP1/SCL2/IOMAF2/RA0)
Volt_Sample1_Reduced: R28.2, R29.1, U2.47 (AD4AN4/CVDAN26/CVDTX10/RP27/SCK2/IOMAF1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)
Volt_Sample2_Reduced: R30.2, R31.1, U2.46 (AD4ANN1/AD4AN2/CVDAN23/CVDTX7/CMP4C/IBI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)
Volt_Sample3_Reduced: R32.2, R33.1, U2.45 (AD4ANN2/AD4AN1/CVDAN22/CVDTX6/CMP/IBIAS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)
Volt_Sample4_Reduced: R34.2, R35.1, U2.44 (PGC1/AD4AN0/CVDAN20/CVDTX4/CMP4B/RP21/S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)
Volt_Sample5_Reduced: R36.2, R37.1, U2.43 (PGD1/AD4AN3/CVDAN19/CVDTX3/CMP4A/RP20/S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)
Volt_Sample6_Reduced: R38.2, R39.1, U2.26 (OA3IN+/AD3AN1/AD4AN5/CVDAN21/CVDTX5/CMP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)
Volt_Sample7_Reduced: R40.2, R41.1, U2.25 (OA3IN-/AD3ANN2/AD3AN2/CVDAN6/CMPDN/CMP3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)
Volt_Sample8_Reduced: R42.2, R43.1, U2.15 (AD1ANN1/AD1AN4/CVDAN10/CMPEN/RP11/RA10)
Volt_Sample9_Reduced: R44.2, R45.1, U2.14 (UREF/AD1AN3/CVDAN9/IBIAS2/ISRC2/RP10/RA9)
Volt_Sample10_Reduced: R46.2, R47.1, U2.13 (DACOUT2/AD5AN3/CVDAN8/IBIAS3/ISRC3/RP9/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)
Volt_Sample11_Reduced: R48.2, R49.1, U2.12 (AD5ANN2/AD5AN2/CVDAN11/CMPFN/RP12/RA11)
Volt_Sample12_Reduced: R50.2, R51.1, U2.5 (AD5ANN1/AD5AN0/CVDAN7/RP8/SDA2/IOMAF1/R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)
fan1_48V: F3.2, J9.2, J11.3, R28.1
fan1_PWM: J9.4, J11.1, U2.52 (RP98/APWM4H/IOMBD11/RG1)
fan1_RTN: J9.1, J11.4, R1.1, U4.3 (+)
fan1_TACH: J9.3, J11.2, R16.2, U2.53 (RP99/APWM4L/IOMBD10/RG2)
fan2_48V: F4.2, J9.6, J12.3, R30.1
fan2_PWM: J9.8, J12.1, U2.64 (PGC3/RP35/PWM4H/IOMAD7/RC2)
fan2_RTN: J9.5, J12.4, R2.1, U4.5 (+)
fan2_TACH: J9.7, J12.2, R17.2, U2.65 (PGD3/RP38/PWM4L/IOMAD6/RC5)
fan3_48V: F5.2, J10.2, J13.3, R32.1
fan3_PWM: J10.4, J13.1, U2.66 (RP36/PWM3H/IOMAD5/RC3)
fan3_RTN: J10.1, J13.4, R3.1, U4.10 (+)
fan3_TACH: J10.3, J13.2, R18.2, U2.67 (RP37/PWM3L/IOMAD4/RC4)
fan4_48V: F6.2, J10.6, J14.3, R34.1
fan4_PWM: J10.8, J14.1, U2.68 (RP43/PWM7H/IOMBD5/IOMBF1/RC10)
fan4_RTN: J10.5, J14.4, R4.1, U4.12 (+)
fan4_TACH: J10.7, J14.2, R19.2, U2.69 (RP44/PWM7L/IOMBD4/IOMBF0/RC11)
fan5_48V: F7.2, J15.2, J17.3, R36.1
fan5_PWM: J15.4, J17.1, U2.70 (RP45/PWM8H/IOMBD7/RC12)
fan5_RTN: J15.1, J17.4, R5.1, U5.3 (+)
fan5_TACH: J15.3, J17.2, R20.2, U2.71 (RP46/PWM8L/IOMBD6/RC13)
fan6_48V: F8.2, J15.6, J19.3, R38.1
fan6_PWM: J15.8, J19.1, U2.74 (RP47/APWM3H/IOMBD9/RC14)
fan6_RTN: J15.5, J19.4, R6.1, U5.5 (+)
fan6_TACH: J15.7, J19.2, R21.2, U2.75 (RP48/APWM3L/IOMBD8/RC15)
fan7_48V: F9.2, J16.2, J20.3, R40.1
fan7_PWM: J16.4, J20.1, U2.76 (RP58/PWM6H/IOMBD3/IOMBF7/RD9)
fan7_RTN: J16.1, J20.4, R7.1, U5.10 (+)
fan7_TACH: J16.3, J20.2, R22.2, U2.77 (RP59/PWM6L/IOMBD2/IOMAF9/IOMBF9/RD10)
fan8_48V: F10.2, J16.6, J18.3, R42.1
fan8_PWM: J16.8, J18.1, U2.78 (RP49/PWM2H/IOMAD3/RD0)
fan8_RTN: J16.5, J18.4, R8.1, U5.12 (+)
fan8_TACH: J16.7, J18.2, R23.2, U2.79 (TCK/RP50/PWM2L/IOMAD2/RD1)
fan9_48V: F11.2, J21.2, J24.3, R44.1
fan9_PWM: J21.4, J24.1, U2.82 (TDO/RP51/PWM1H/IOMAD1/RD2)
fan9_RTN: J21.1, J24.4, R9.1, U6.3 (+)
fan9_TACH: J21.3, J24.2, R24.2, U2.83 (TDI/RP52/PWM1L/IOMAD0/RD3)
fan10_48V: F12.2, J21.6, J25.3, R46.1
fan10_PWM: J21.8, J25.1, U2.90 (RP54/PWM5H/ASCL1/IOMBD1/RD5)
fan10_RTN: J21.5, J25.4, R10.1, U6.5 (+)
fan10_TACH: J21.7, J25.2, R25.2, U2.91 (RP55/PWM5L/ASDA1/IOMBD0/RD6)
fan11_48V: F13.2, J22.2, J23.3, R48.1
fan11_PWM: J22.4, J23.1, U2.93 (RP60/APWM1H/IOMAD9/IOMAF8/IOMBF8/RD11)
fan11_RTN: J22.1, J23.4, R11.1, U6.10 (+)
fan11_TACH: J22.3, J23.2, R26.2, U2.94 (RP61/ASDA3/RD12)
fan12_48V: F14.2, J22.6, J26.3, R50.1
fan12_PWM: J22.8, J26.1, U2.96 (RP63/APWM2H/IOMAD11/RD14)
fan12_RTN: J22.5, J26.4, R12.1, U6.12 (+)
fan12_TACH: J22.7, J26.2, R27.2, U2.97 (RP64/APWM2L/IOMAD10/IOMBF5/RD15)
